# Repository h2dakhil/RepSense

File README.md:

# Wrist Fitness Tracker — Custom PCB

A wrist-mounted, watch-form wearable that detects and counts gym exercise reps in real time using an IMU and sensor fusion. Built around a circular 42 mm custom PCB designed for low power, low cost, and size-constrained wearable use.

Inspired by the Apple Watch workout detection feature but built from scratch — custom hardware, custom firmware, no cloud dependency.

---

## Overview

The device sits on the wrist like a watch. It reads 6-axis motion data from an IMU, runs an Extended Kalman Filter (EKF) to fuse accelerometer and gyroscope data into a clean orientation estimate, and uses that to detect and count repetitions for exercises including:

- Bicep curl
- Shoulder press
- Bench press
- Lateral raise
- Squat
- Deadlift
- Overhead press

Rep count and exercise type are displayed in real time on a small OLED screen. The entire signal processing pipeline runs on-device with no wireless transmission required in v1.

---

## Hardware

### System block diagram

### MCU — nRF52840 QIAA QFN73

Nordic's nRF52840 was selected because it satisfies every constraint in a single chip with no external LDO required:

- Cortex-M4F at 64 MHz with hardware floating point — needed for EKF math
- Native USB (D+/D−) — drag-and-drop UF2 firmware flashing, no UART bridge chip
- BLE 5.0 built in — phone integration ready for v2 with no extra hardware
- Internal DC-DC converter (DCDCEN0) — steps VDDH down to 3.3V internally, powers entire board via EXTSUPPLY rail
- 1.5 µA deep sleep with wake-on-interrupt — critical for wearable battery life
- VDDH accepts up to 5.5V — direct PMIC output connection, no external LDO needed
- Same chip as the Seeed XIAO nRF52840 Sense used for firmware feasibility validation

**Circuit configuration:** Nordic Config 4 (High Voltage mode, DCDCEN0 enabled, USB enabled, NFC disabled). The PMIC SYS output feeds VDDH directly. The chip's internal REG0 DC-DC produces a stable 3.3V on VDD which is exposed as the board's entire 3.3V supply rail via EXTSUPPLY. One 10 µH inductor on DCCH is the only passive required for this configuration.

**Programming:** First-time bootloader flash via SWD using a J-Link EDU Mini and Tag-Connect TC2030-IDC-NL pads on the PCB. After the Adafruit UF2 bootloader is installed, all subsequent firmware updates are drag-and-drop `.uf2` over USB — identical to the Seeed dev board experience.

**Package selection:** QFN48 was considered and rejected. The QFN48 does not expose D+, D−, or VBUS — USB is physically absent. QFN73 is required. The 1 mm size difference per side is irrelevant at 42 mm PCB diameter.

### IMU — LSM6DSVTR

ST's LSM6DSV was selected for its onboard sensor fusion engine and FSM (Finite State Machine) which offload motion processing from the MCU:

- 6-axis: 3-axis accelerometer (±2 to ±16 g) + 3-axis gyroscope (up to 4000 dps)
- Onboard sensor fusion reduces MCU interrupt load
- Programmable FSM enables gesture and motion pattern detection in hardware
- Large FIFO for buffered data collection, reducing MCU wake frequency
- Low power always-on mode for wrist-raise and motion-triggered wake
- I2C interface, address 0x6A (SA0 pulled to GND)
- INT1 routed to P1.06 — configured as wake-on-motion interrupt

INT1 is the key to efficient battery use. The nRF52840 sleeps at 1.5 µA. When the IMU detects motion above a threshold it pulls INT1 high, waking the MCU instantly. The MCU only runs the rep counting pipeline while the user is actively moving. Between sets and between sessions the system is effectively off.

**I2C pin assignment:** SDA → P1.04, SCL → P1.05, INT1 → P1.06

### PMIC — BQ24074RGTR

TI's BQ24074 handles charging and system power path in a single 3×3 mm QFN:

- Dynamic Power Path Management (DPPM) — simultaneously powers system and charges battery from USB, reducing battery charge/discharge cycles
- USB500 mode selected (EN1 high, EN2 low) — 500 mA input limit, leaves ~400 mA headroom for system after 100 mA charge current
- Charge current set to 100 mA (0.5C for 200 mAh cell) via 9 kΩ ISET resistor
- Input range 4.35–10.5V — compatible with USB 5V
- OVP, thermal regulation, reverse current, and short-circuit protection built in
- TS pin tied to 10 kΩ to GND — battery has no NTC thermistor, this prevents false thermal fault

### Display

0.91" SSD1306 OLED, 128×32 monochrome, I2C address 0x78. Shares I2C bus with IMU — no address conflict. Max 30 mA. Soldered directly to 4× 2.54 mm PTH pads on PCB. Onboard module pullup resistors (4.7 kΩ) serve the entire I2C bus.

### Battery

302035 LiPo, 3.7V nominal, 200 mAh, JST-PH 2 mm 2-pin. Dimensions 36×20×3 mm. Includes onboard protection PCB (OVP, overdischarge, short circuit). Charge current 100 mA (0.5C).

Battery voltage monitored via 1 MΩ/1 MΩ resistor divider to nRF52840 AIN pin for on-screen battery percentage.

---

## Power budget

Design target: low enough average current draw to sustain multi-hour gym sessions on a 200 mAh cell.

### Active current draw (during rep counting)

| Component | Current | Notes |
|---|---|---|
| nRF52840 (active, no BLE) | ~5 mA | Cortex-M4 running EKF + display update |
| LSM6DSV IMU | ~0.35 mA | 3.3V estimated from 0.65 mA at 1.8V |
| OLED display | ~20 mA | Typical for 128×32 at moderate brightness |
| PMIC quiescent | ~0.05 mA | BQ24074 Iq |
| Resistor divider | ~0.002 mA | 2.1 µA, negligible |
| **Total active** | **~25.4 mA** | |

### Sleep current (between sets / idle)

| Component | Current | Notes |
|---|---|---|
| nRF52840 (System ON, wake on RTC) | 1.5 µA | Nordic spec, no RAM retention |
| LSM6DSV (low power accel only) | ~25 µA | Motion detection active, waiting for INT1 |
| OLED display (off) | ~5 µA | Controller standby |
| **Total sleep** | **~32 µA** | |

### Runtime estimate

Assuming a typical 1-hour gym session: 20 minutes active (rep counting) + 40 minutes rest (sleep between sets):

```
Active:  20 min × 25.4 mA  = 508 mAh-min
Sleep:   40 min × 0.032 mA = 1.28 mAh-min
Total:   509 mAh-min / 60  = ~8.5 mAh per session
```

On a 200 mAh cell (usable ~160 mAh accounting for LDO dropout margin):

```
160 mAh / 8.5 mAh per session ≈ ~18 full gym sessions per charge
```

For all-day wear with occasional active periods, sleep current dominates — 32 µA into 200 mAh gives over 250 days of idle standby. In practice charge weekly.

### Battery monitoring

Resistor divider (1 MΩ / 1 MΩ) scales VBAT to half voltage at the ADC pin:

| Battery state | VBAT | AIN voltage | 12-bit ADC count |
|---|---|---|---|
| Full | 4.20 V | 2.10 V | 2606 |
| 75% | 3.90 V | 1.95 V | 2420 |
| 50% | 3.70 V | 1.85 V | 2296 |
| 25% | 3.50 V | 1.75 V | 2172 |
| Low | 3.20 V | 1.60 V | 1986 |

Firmware reverse calculation: `VBAT = ADC_count × 6.6 / 4096`

Divider quiescent drain: 2.1 µA — equivalent to 5.4 years of drain on this cell. Negligible.

---

## Firmware architecture

### Sensing pipeline

```
IMU (6-axis raw) → EKF sensor fusion → orientation estimate
                                              │
                                    rep detection algorithm
                                              │
                                    exercise classifier (heuristic v1)
                                              │
                                       display update
```

### Extended Kalman Filter (EKF)

Raw accelerometer and gyroscope data are fused using an EKF:

- **Prediction step:** gyroscope data integrates orientation forward in time — fast but drifts
- **Correction step:** accelerometer gravity vector corrects the drift — slow but absolute
- **Output:** clean, drift-free quaternion orientation estimate

On a wrist-mounted IMU, gravity rotates in the body frame throughout each rep. This rotation is both the challenge (it confounds raw accelerometer rep detection) and the signal (it gives the EKF its correction input). The EKF output removes gravity ambiguity and produces a clean tilt signal that reps appear as clear periodic waves in.

The nRF52840 Cortex-M4F with hardware floating point handles EKF math at >500 Hz comfortably.

### Rep detection

Per rep, the following features are extracted from the EKF orientation output:

- Dominant motion axis (principal direction of angular change)
- Range of motion in degrees
- Rep duration
- Peak angular velocity
- Zero-crossing frequency

**v1 — Heuristic classifier:** if/else rules on extracted features. Fast, interpretable, no training data required. Handles 5–8 distinct exercises reliably.

**v2 — TinyML:** TensorFlow Lite Micro CNN/MLP on rep window. Better generalisation across users and subtle exercise variations. Planned once v1 heuristics are validated.

### Exercise detection logic

Each exercise has a distinct wrist motion signature:

| Exercise | Primary axis | Motion signature |
|---|---|---|
| Bicep curl | Pitch (wrist rotates forward) | Large pitch swing, ~120° ROM, 1–2 s period |
| Shoulder press | Vertical translation dominant | High Z accel, moderate pitch, pressing pattern |
| Bench press | Elbow extension dominant | Moderate pitch, low ROM, bilateral pattern |
| Lateral raise | Roll (arm lifts sideways) | Large roll swing, ~90° ROM |
| Squat | Body pitch with knee flexion | Slow deep pitch oscillation, ~3–4 s |
| Deadlift | Hip hinge dominant | Large pitch, high peak accel on concentric |
| Overhead press | Similar to shoulder press | Higher ROM, full elbow extension signature |

The classifier reads the dominant axis, ROM range, and rep cadence. Most exercises are distinct enough that a threshold-based decision tree separates them reliably. Exercises with similar signatures (shoulder press vs overhead press) are disambiguated by ROM magnitude.

### Wake-on-motion

IMU INT1 configured as motion-detect interrupt → nRF52840 GPIO wakeup. MCU stays in System ON sleep (1.5 µA) until motion above threshold detected. Eliminates polling entirely.

---

## PCB

- **Form factor:** circular, 42 mm diameter
- **Layers:** 2
- **Manufacturer:** JLCPCB (fabrication + assembly)
- **Assembly:** JLCPCB SMT — nRF52840 QFN73, BQ24074 QFN16, LSM6DSV LGA14 all assembled
- **Programming interface:** Tag-Connect TC2030-IDC-NL pads (no legs, flush with PCB surface)
- **Reset:** SMD momentary button, RESET pin → GND, 10 kΩ pullup, 100 nF filter cap
- **Antenna:** unpopulated in v1 (BLE not enabled). RF matching network footprints retained DNP for v2 population without board respin
- **Crystal:** 32 MHz SMD2016 (YXC X2016 32MKB4SI, LCSC C718072) mandatory main clock. 32.768 kHz RTC crystal footprint DNP for v2

---

## Estimated unit cost

Based on JLCPCB pricing at low volume (5 units):

| Item | Est. cost (USD) |
|---|---|
| PCB fabrication (5× circular 42 mm, 2-layer) | ~$2.00/unit |
| nRF52840 QIAA QFN73 (LCSC C190794) | ~$6.50 |
| LSM6DSVTR IMU | ~$3.50 |
| BQ24074RGTR PMIC | ~$2.50 |
| 32 MHz crystal | ~$0.10 |
| 10 µH inductor (DCCH) | ~$0.15 |
| Passives (caps, resistors, ESD) | ~$0.50 |
| USB-C connector | ~$0.30 |
| JST-PH battery connector | ~$0.20 |
| OLED display module | ~$3.00 |
| LiPo 302035 200 mAh | ~$3.00 |
| JLCPCB SMT assembly fee (est.) | ~$8.00 |
| **Total per unit (5-unit run)** | **~$29.75** |

Cost drops significantly at higher volumes — MCU and PMIC pricing improves at 50+ units and assembly amortises across more boards.

---

## Feasibility validation

Before committing to the custom PCB, the full sensing pipeline was prototyped and validated on a **Seeed XIAO nRF52840 Sense** development board. This board uses the same nRF52840 MCU and includes an onboard LSM6DS3 IMU (predecessor to the LSM6DSV used in the final design).

Validation confirmed:
- IMU data acquisition over I2C at the required sample rate
- Raw accelerometer and gyroscope signal quality for rep detection
- Wrist-mounted motion signatures are clearly periodic and distinguishable per exercise
- nRF52840 toolchain (Adafruit nRF52 Arduino framework) workflow — compile, UF2 drag-and-drop flash, serial monitor
- EKF algorithm correctness on real motion data before hardware commitment

The custom PCB is a direct hardware consolidation of the validated dev board pipeline — same MCU, same firmware framework, same IMU family — into a circular wearable form factor.

---

## Repository structure

```
/firmware          nRF52840 Arduino/PlatformIO firmware
/hardware          KiCad schematic and PCB layout files
/docs              design notes, component datasheets, calculations
/data              CSV motion logs from feasibility phase
README.md
```

---

## Roadmap

| Version | Status | Description |
|---|---|---|
| v1 | In progress | Custom PCB, heuristic rep counter, OLED display, 5 exercises |
| v2 | Planned | BLE to iPhone, TinyML classifier, 10+ exercises, OTA firmware updates |
| v3 | Future | Custom enclosure, production-ready assembly, refined form factor |

---

## Design constraints summary

| Constraint | Approach |
|---|---|
| Size | 42 mm circular PCB, no external LDO, all ICs QFN/LGA |
| Low power | nRF52840 1.5 µA sleep, IMU wake-on-motion INT1, display off between updates |
| Low cost | ~$30/unit at 5 units, ~$18 at volume; single-sided JLCPCB assembly |
| Programmability | Native USB UF2 after one-time SWD bootloader flash |
| Sensor accuracy | EKF fusion eliminates gyro drift and gravity confusion on raw accel |

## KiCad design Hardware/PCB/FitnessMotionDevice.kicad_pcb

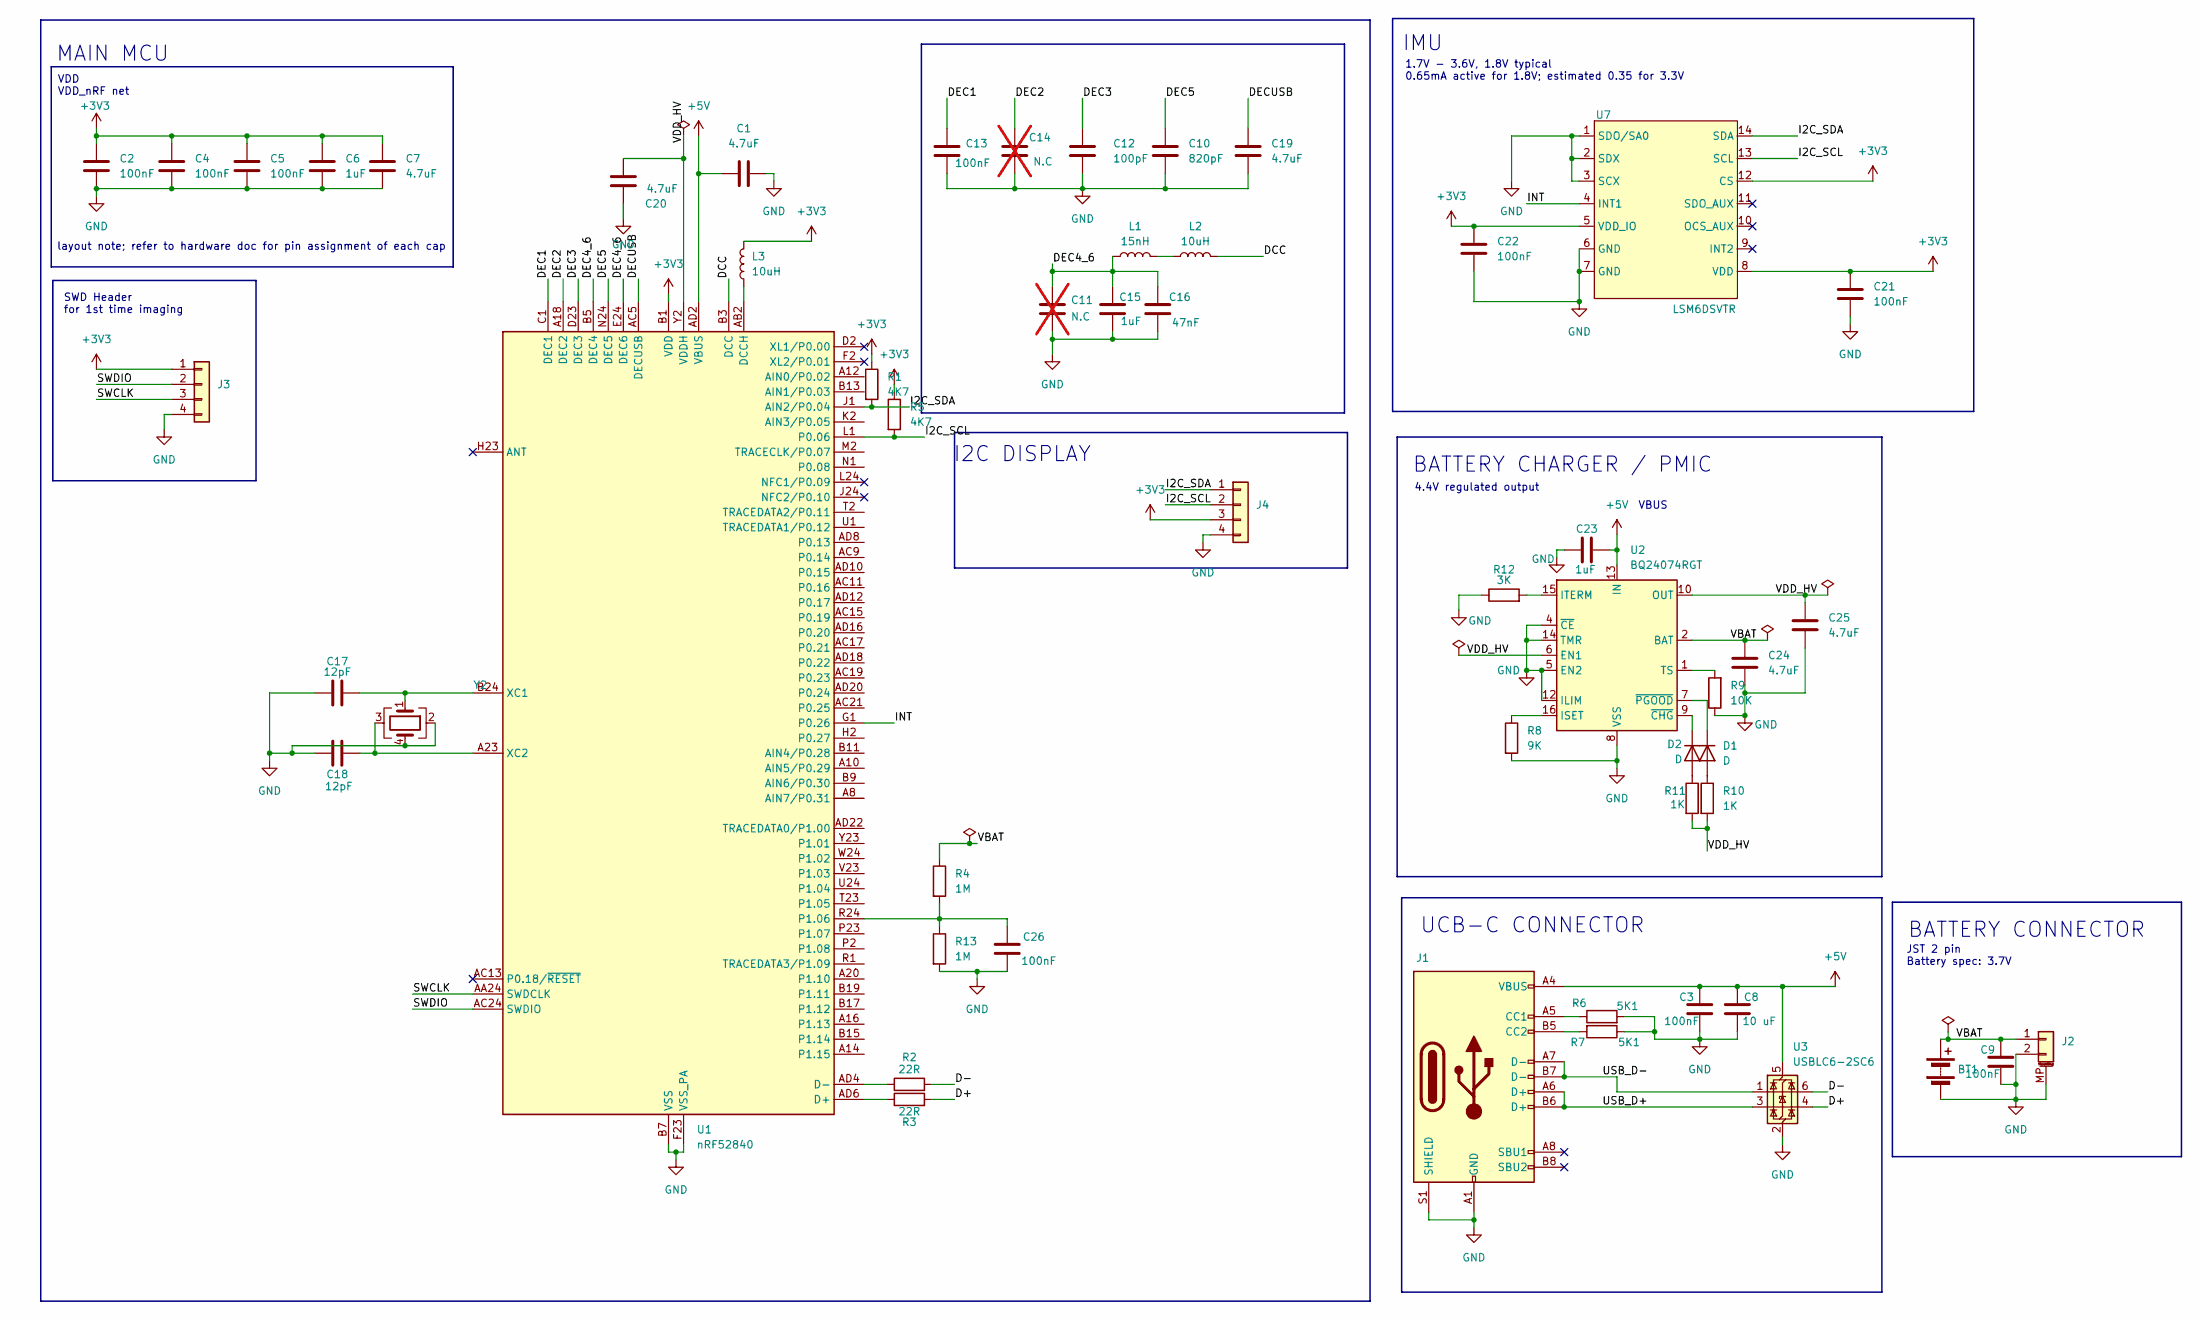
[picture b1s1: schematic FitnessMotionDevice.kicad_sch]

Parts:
BT1: Battery
C1, C20, C24, C25: 4.7uF; C_0603_1608Metric; LCSC C385034
C2, C4, C5, C21, C22: 100nF; C_0402_1005Metric; LCSC C60474
C3, C9, C26: 100nF; C_0603_1608Metric; LCSC C14663
C6, C23: 1uF; C_0603_1608Metric; LCSC C29936
C7, C19: 4.7uF; C_0603_1608Metric; LCSC C389010
C8: 10 uF; C_1206_3216Metric_Pad1.33x1.80mm_HandSolder; LCSC C89632
C10: 820pF; C_0402_1005Metric; LCSC C726612
C11, C14: N.C; C_0402_1005Metric; not fitted
C12: 100pF; C_0402_1005Metric; LCSC C106200
C13: 100nF; C_0402_1005Metric
C15: 1uF; C_0603_1608Metric
C16: 47nF; C_0402_1005Metric; LCSC C272875
C17, C18: 12pF; C_0402_1005Metric; LCSC C326662
D1, D2: D; LED_0805_2012Metric; LCSC C19171391
J1: USB_C_Receptacle_USB2.0_16P; USB_C_Receptacle_HRO_TYPE-C-31-M-12; LCSC C2765186
J2: Conn_01x02_MountingPin; JST_PH_S2B-PH-SM4-TB_1x02-1MP_P2.00mm_Horizontal; LCSC C295747
J3: Conn_01x04; Tag-Connect_TC2030-IDC-NL_2x03_P1.27mm_Vertical
J4: Conn_01x04; PinHeader_1x04_P2.54mm_Vertical
L1: 15nH; L_0402_1005Metric; LCSC C98055
L2: 10uH; L_0603_1608Metric; LCSC C86083
L3: 10uH; L_0603_1608Metric; LCSC C76798
R1, R5: 4K7; R_0402_1005Metric; LCSC C105871
R2, R3: 22R; R_0402_1005Metric; LCSC C114765
R4, R13: 1M; R_0402_1005Metric; LCSC C138033
R6, R7: 5K1; R_0603_1608Metric_Pad0.98x0.95mm_HandSolder; LCSC C2907044
R8: 9K; R_0805_2012Metric; LCSC C2930212
R9: 10K; R_0402_1005Metric; LCSC C60490
R10, R11: 1K; R_0402_1005Metric; LCSC C106235
R12: 3K; R_0603_1608Metric; LCSC C2907033
U1: nRF52840; Nordic_AQFN-73-1EP_7x7mm_P0.5mm; LCSC C190794
U2: BQ24074RGT; VQFN-16-1EP_3x3mm_P0.5mm_EP1.6x1.6mm; LCSC C54313
U3: USBLC6-2SC6; SOT-23-6; LCSC C7519
U7: LSM6DSVTR; LGA14-L_2P59X3P1X0P5_STM; LCSC C5267399
Y2: Crystal_GND23; Crystal_SMD_2016-4Pin_2.0x1.6mm

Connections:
+3V3: C2.1, C4.1, C5.1, C6.1, C7.1, C21.1, C22.1, J3.1, J4.3, L3.2, R1.1, R5.1, U1.A22 (VDD), U1.AD14 (VDD), U1.AD23 (VDD), U1.B1 (VDD), U1.W1 (VDD), U7.5 (VDD_IO), U7.8 (VDD), U7.12 (CS); also elsewhere on the board
+5V: C1.2, C3.2, C8.2, C23.2, J1.A4 (VBUS), J1.A9 (VBUS), J1.B4 (VBUS), J1.B9 (VBUS), U1.AD2 (VBUS), U2.13 (IN), U3.5 (VBUS); also elsewhere on the board
/D+: R3.2, U3.4 (I/O2)
/D-: R2.2, U3.6 (I/O1)
/DCC: L2.2, U1.B3 (DCC)
/DEC1: C13.1, U1.C1 (DEC1)
/DEC2: C14.1, U1.A18 (DEC2)
/DEC3: C12.1, U1.D23 (DEC3)
/DEC4_6: C11.1, C15.1, C16.1, L1.1, U1.B5 (DEC4), U1.E24 (DEC6)
/DEC5: C10.1, U1.N24 (DEC5)
/DECUSB: C19.1, U1.AC5 (DECUSB)
/I2C_SCL: J4.2, R5.2, U1.L1 (P0.06), U7.13 (SCL)
/I2C_SDA: J4.1, R1.2, U1.J1 (AIN2/P0.04), U7.14 (SDA)
/INT: U1.G1 (P0.26), U7.4 (INT1)
/SWCLK: J3.3, U1.AA24 (SWDCLK)
/SWDIO: J3.2, U1.AC24 (SWDIO)
/USB_D+: J1.A6 (D+), J1.B6 (D+), U3.3 (I/O2)
/USB_D-: J1.A7 (D-), J1.B7 (D-), U3.1 (I/O1)
/VBAT: BT1.1 (+), C9.2, C24.1, J2.1, R4.1, U2.2 (BAT), U2.3 (BAT); also elsewhere on the board
/VDD_HV: C20.1, C25.1, R10.2, R11.2, U1.Y2 (VDDH), U2.6 (EN1), U2.10 (OUT), U2.11 (OUT)
GND: BT1.2 (-), C1.1, C2.2, C3.1, C4.2, C5.2, C6.2, C7.2, C8.1, C9.1, C10.2, C11.2, C12.2, C13.2, C14.2, C15.2, C16.2, C17.1, C18.2, C19.2, C20.2, C21.2, C22.2, C23.1, C24.2, C25.2, C26.1, J1.A1 (GND), J1.A12 (GND), J1.B1 (GND), J1.B12 (GND), J1.S1 (SHIELD), J2.2, J2.MP (MountPin), J3.4, J4.4, R6.2, R7.1, R8.2, R9.1, R12.1, R13.2, U1.B7 (VSS), U1.EP (VSS), U1.F23 (VSS_PA), U2.4 (~CE), U2.5 (EN2), U2.8 (VSS), U2.12 (ILIM), U2.14 (TMR), U2.17 (VSS), U3.2 (GND), U7.1 (SDO/SA0), U7.2 (SDX), U7.3 (SCX), U7.6 (GND), U7.7 (GND), Y2.2, Y2.4; also elsewhere on the board
unnamed: D1.2 (A), R10.1
unnamed: D1.1 (K), U2.7 (~PGOOD)
unnamed: D2.2 (A), R11.1
unnamed: D2.1 (K), U2.9 (~CHG)
unnamed: J1.A5 (CC1), R6.1
unnamed: J1.B5 (CC2), R7.2
unnamed: L1.2, L2.1
unnamed: R3.1, U1.AD6 (D+)
unnamed: R2.1, U1.AD4 (D-)
unnamed: L3.1, U1.AB2 (DCCH)
unnamed: C26.2, R4.2, R13.1, U1.R24 (P1.06)
unnamed: C17.2, U1.B24 (XC1), Y2.1
unnamed: C18.1, U1.A23 (XC2), Y2.3
unnamed: R8.1, U2.16 (ISET)
unnamed: R12.2, U2.15 (ITERM)
unnamed: R9.2, U2.1 (TS)

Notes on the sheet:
MAIN MCU
I2C DISPLAY
JST 2 pin Battery spec: 3.7V
UCB-C CONNECTOR
BATTERY CONNECTOR
SWD Header for 1st time imaging
VBUS
IMU
layout note; refer to hardware doc for pin assignment of each cap
VDD VDD_nRF net
4.4V regulated output
1.7V - 3.6V, 1.8V typical 0.65mA active for 1.8V; estimated 0.35 for 3.3V
BATTERY CHARGER / PMIC

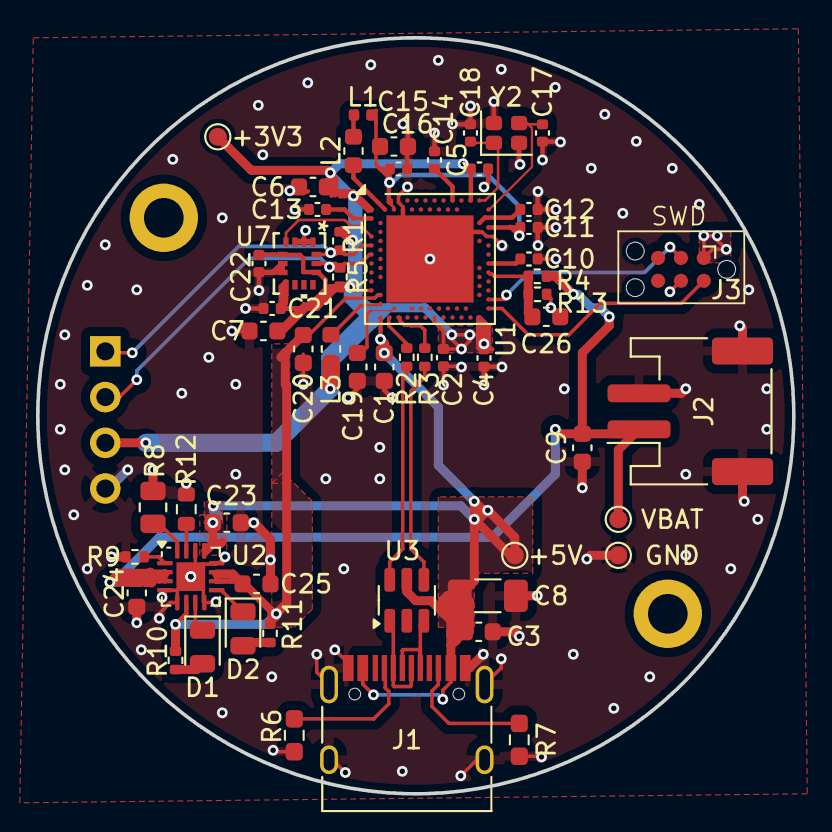
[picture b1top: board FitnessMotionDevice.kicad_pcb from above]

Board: 2 copper layers, 42.0 x 42.0 mm, 57 parts (1 on the bottom side), 37 nets.

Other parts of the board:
+3V3, +5V: TestPoint_Pad_D1.0mm
GND: TestPoint_Pad_D1.0mm
VBAT: TestPoint_Pad_D1.0mm

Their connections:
+3V3: +3V3.1; also elsewhere on the board
+5V: +5V.1; also elsewhere on the board
/VBAT: VBAT.1; also elsewhere on the board
GND: GND.1; also elsewhere on the board

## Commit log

2026-05-14 added readme
2026-05-14 updated readme
    Removed system block diagram from README.md.
2026-05-15 update firmware
